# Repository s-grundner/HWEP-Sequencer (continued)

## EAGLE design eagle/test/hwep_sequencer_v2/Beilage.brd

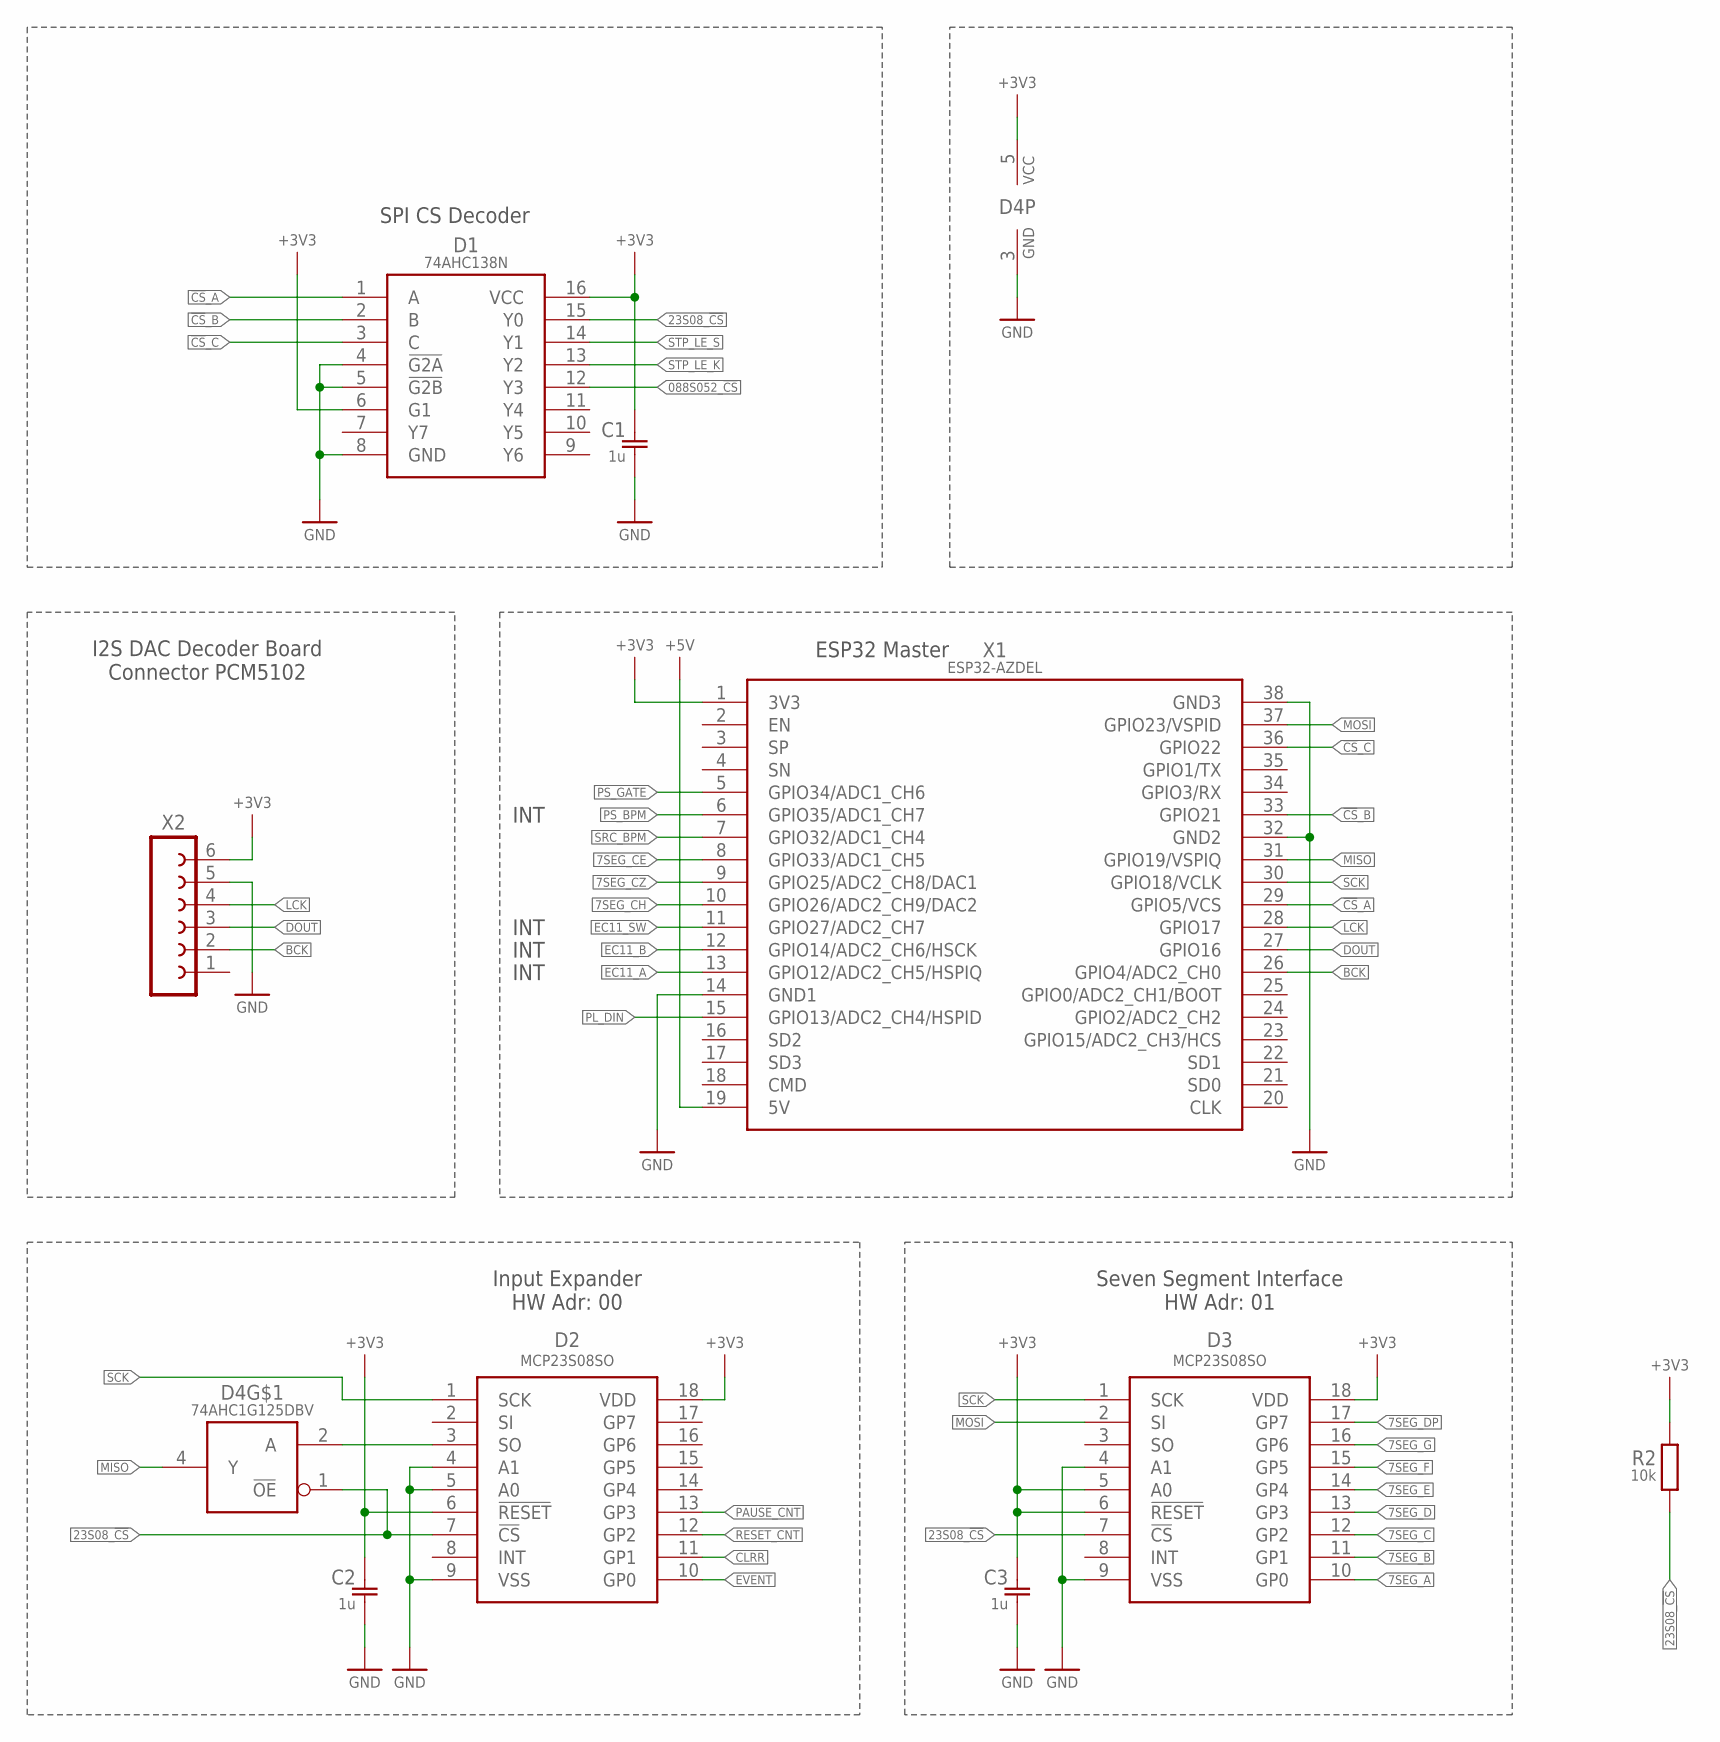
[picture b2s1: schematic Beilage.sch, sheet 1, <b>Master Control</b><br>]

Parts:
C1, C2, C3: 1u; C0805
D1: 74AHC138N; DIP16
D2, D3: MCP23S08SO; SO18W
D4: 74AHC1G125DBV; SOT23-5
R2: 10k; R0805
X1: ESP32-AZDEL
X2: FE06-1; FE06

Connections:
7SEG_A: D3.10 (GP0); also elsewhere on the board
7SEG_B: D3.11 (GP1); also elsewhere on the board
7SEG_C: D3.12 (GP2); also elsewhere on the board
7SEG_CE: X1.8 (GPIO33/ADC1_CH5); also elsewhere on the board
7SEG_CH: X1.10 (GPIO26/ADC2_CH9/DAC2); also elsewhere on the board
7SEG_CZ: X1.9 (GPIO25/ADC2_CH8/DAC1); also elsewhere on the board
7SEG_D: D3.13 (GP3); also elsewhere on the board
7SEG_DP: D3.17 (GP7); also elsewhere on the board
7SEG_E: D3.14 (GP4); also elsewhere on the board
7SEG_F: D3.15 (GP5); also elsewhere on the board
7SEG_G: D3.16 (GP6); also elsewhere on the board
23S08_!CS: D1.15 (Y0), D2.7 (!CS), D3.7 (!CS), D4.1 (!OE), R2.1
088S052_!CS!: D1.12 (Y3); also elsewhere on the board
!CS!_A: D1.1 (A), X1.29 (GPIO5/VCS)
!CS!_B: D1.2 (B), X1.33 (GPIO21)
!CS!_C: D1.3 (C), X1.36 (GPIO22)
+3V3: C1.1, C2.1, C3.1, D1.6 (G1), D1.16 (VCC), D2.6 (!RESET), D2.18 (VDD), D3.5 (A0), D3.6 (!RESET), D3.18 (VDD), D4.5 (VCC), R2.2, X1.1 (3V3), X2.6; also elsewhere on the board
+5V: X1.19 (5V); also elsewhere on the board
BCK: X1.26 (GPIO4/ADC2_CH0), X2.2
CLRR: D2.11 (GP1); also elsewhere on the board
DOUT: X1.27 (GPIO16), X2.3
EC11_A: X1.13 (GPIO12/ADC2_CH5/HSPIQ); also elsewhere on the board
EC11_B: X1.12 (GPIO14/ADC2_CH6/HSCK); also elsewhere on the board
EC11_SW: X1.11 (GPIO27/ADC2_CH7); also elsewhere on the board
EVENT: D2.10 (GP0); also elsewhere on the board
GND: C1.2, C2.2, C3.2, D1.4 (!G2A), D1.5 (!G2B), D1.8 (GND), D2.4 (A1), D2.5 (A0), D2.9 (VSS), D3.4 (A1), D3.9 (VSS), D4.3 (GND), X1.14 (GND1), X1.32 (GND2), X1.38 (GND3), X2.5; also elsewhere on the board
LCK: X1.28 (GPIO17), X2.4
MISO: D4.4 (Y), X1.31 (GPIO19/VSPIQ); also elsewhere on the board
MOSI: D3.2 (SI), X1.37 (GPIO23/VSPID); also elsewhere on the board
unnamed: D2.3 (SO), D4.2 (A)
PAUSE_CNT: D2.13 (GP3); also elsewhere on the board
PL_DIN: X1.15 (GPIO13/ADC2_CH4/HSPID); also elsewhere on the board
PS_BPM: X1.6 (GPIO35/ADC1_CH7); also elsewhere on the board
PS_GATE: X1.5 (GPIO34/ADC1_CH6); also elsewhere on the board
RESET_CNT: D2.12 (GP2); also elsewhere on the board
SCK: D2.1 (SCK), D3.1 (SCK), X1.30 (GPIO18/VCLK); also elsewhere on the board
SRC_BPM: X1.7 (GPIO32/ADC1_CH4); also elsewhere on the board
STP_LE_K: D1.13 (Y2); also elsewhere on the board
STP_LE_S: D1.14 (Y1); also elsewhere on the board

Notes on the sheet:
Seven Segment Interface HW Adr: 01
ESP32 Master
I2S DAC Decoder Board Connector PCM5102
INT
Input Expander HW Adr: 00
SPI CS Decoder

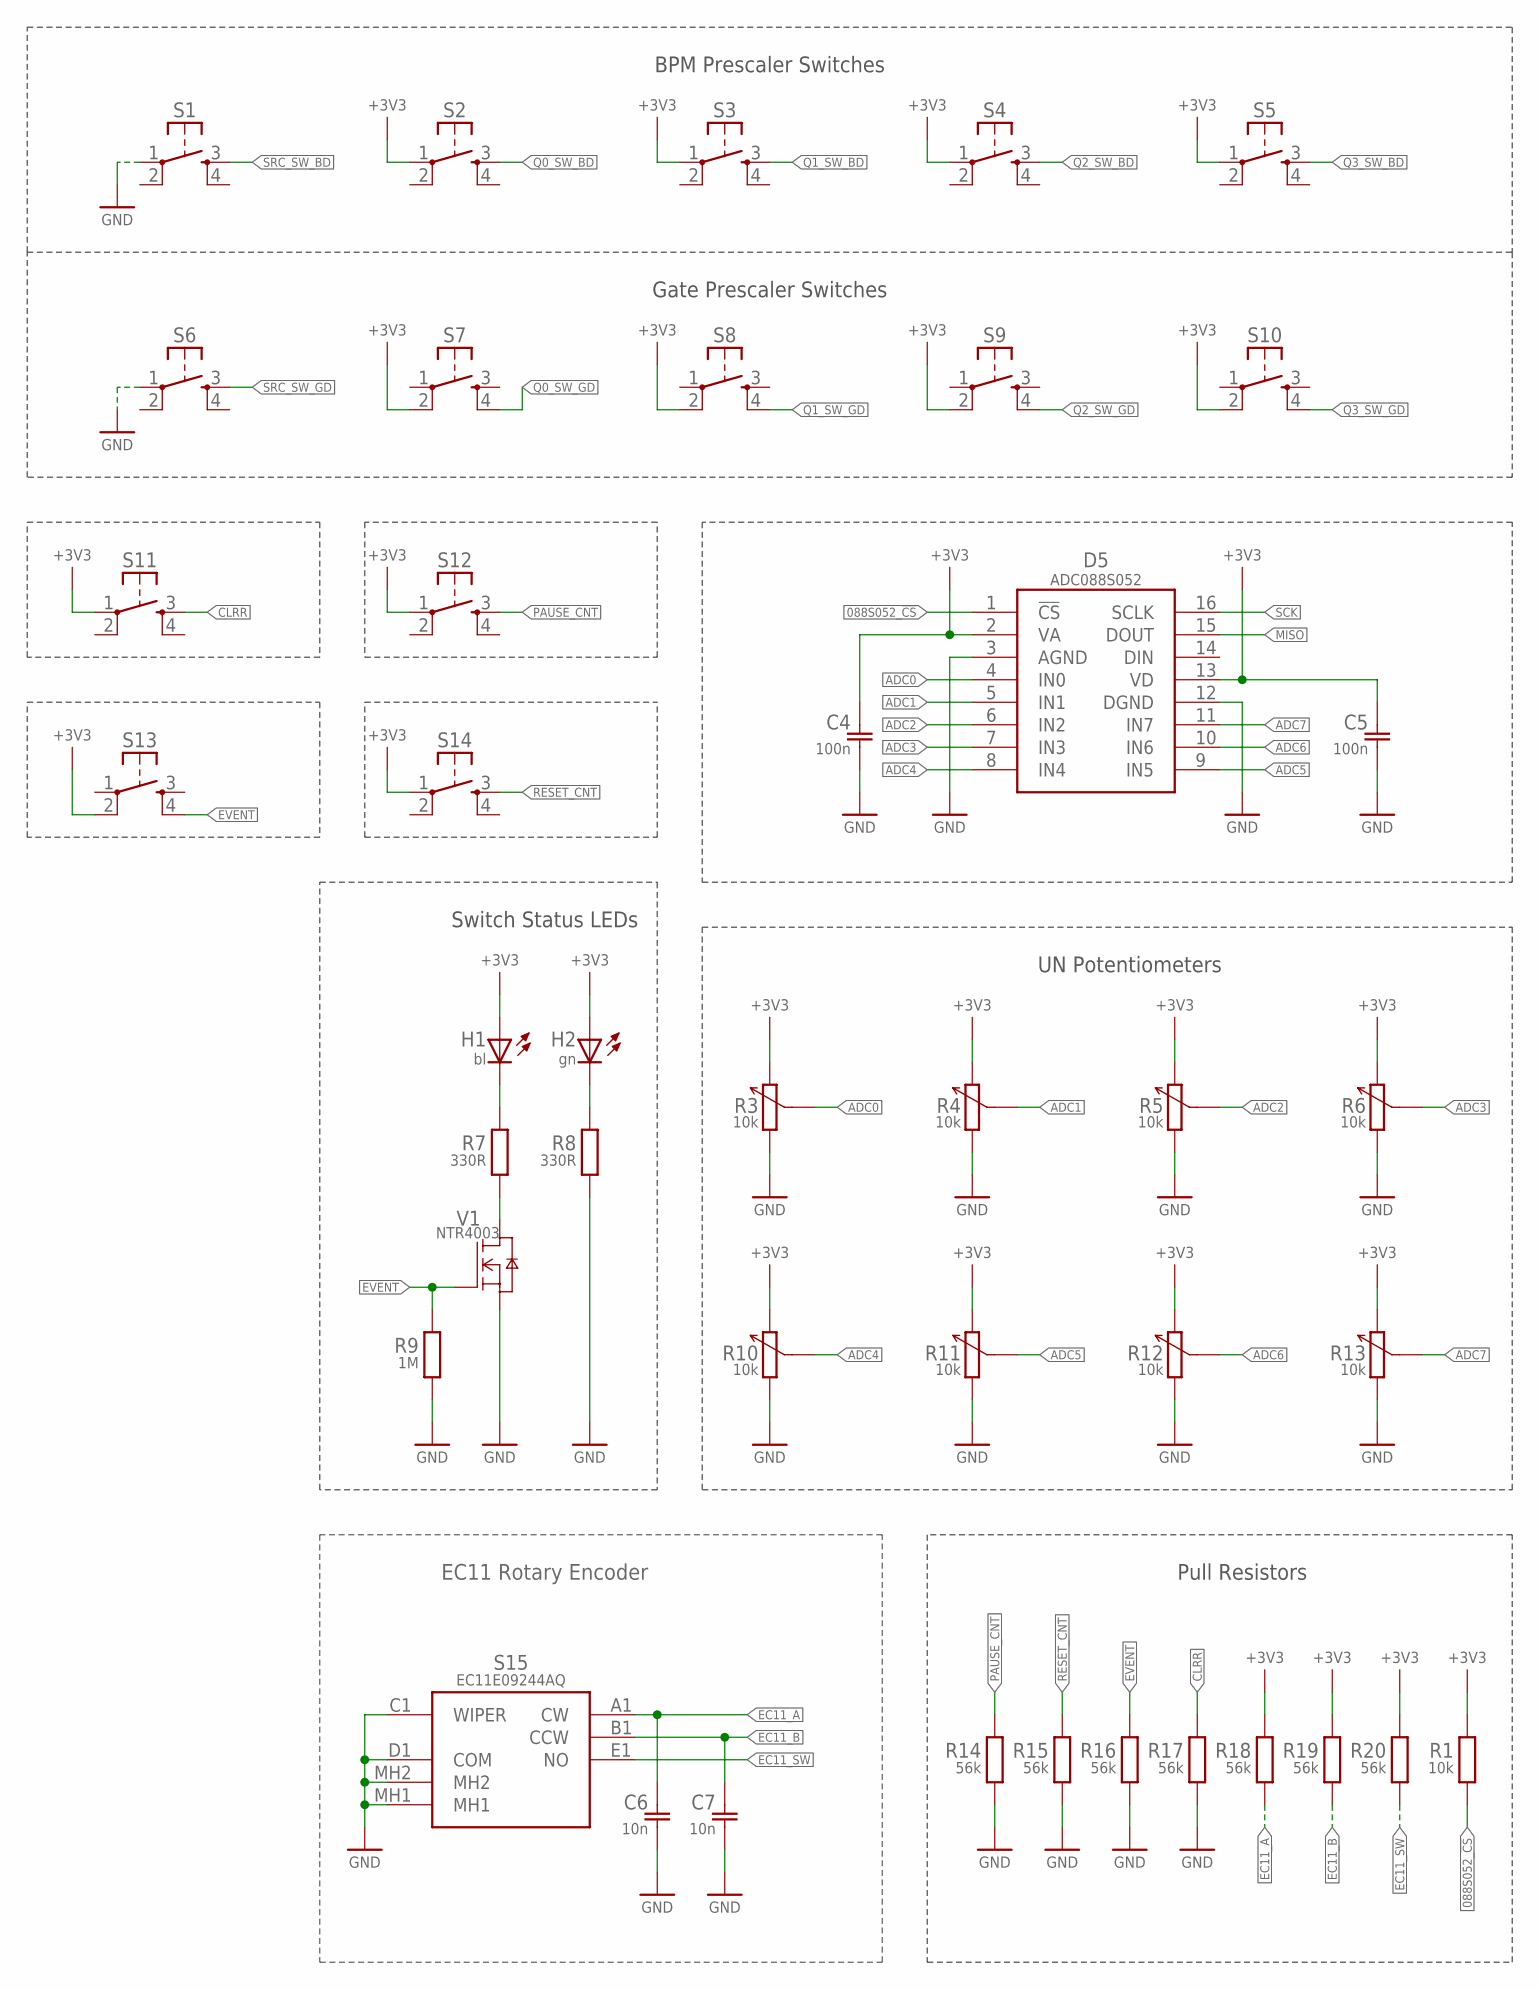
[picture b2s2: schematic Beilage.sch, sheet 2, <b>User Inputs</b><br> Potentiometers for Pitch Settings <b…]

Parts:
C4, C5: 100n; C0805
C6, C7: 10n; C0805
D5: ADC088S052; TSSOP16
H1: bl; CHIPLED_1206
H2: gn; CHIPLED_1206
R1: 10k; R0805
R3, R4, R5, R6, R10, R11, R12, R13: 10k; P160L
R7, R8: 330R; R0805
R9: 1M; R0805
R14, R15, R16, R17, R18, R19, R20: 56k; R0805
S1, S2, S3, S4, S5, S6, S7, S8, S9, S10, S11, S12, S13, S14: TASTE10XX; B3F-10XX
S15: EC11E09244AQ; EC11
V1: NTR4003; SOT23

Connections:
088S052_!CS!: D5.1 (!CS), R1.1; also elsewhere on the board
+3V3: C4.1, C5.1, D5.2 (VA), D5.13 (VD), H1.A, H2.A, R1.2, R3.3 (2), R4.3 (2), R5.3 (2), R6.3 (2), R10.3 (2), R11.3 (2), R12.3 (2), R13.3 (2), R18.2, R19.2, R20.2, S2.1, S3.1, S4.1, S5.1, S7.2 (P1), S8.2 (P1), S9.2 (P1), S10.2 (P1), S11.1, S12.1, S13.2 (P1), S14.1; also elsewhere on the board
ADC0: D5.4 (IN0), R3.2 (3)
ADC1: D5.5 (IN1), R4.2 (3)
ADC2: D5.6 (IN2), R5.2 (3)
ADC3: D5.7 (IN3), R6.2 (3)
ADC4: D5.8 (IN4), R10.2 (3)
ADC5: D5.9 (IN5), R11.2 (3)
ADC6: D5.10 (IN6), R12.2 (3)
ADC7: D5.11 (IN7), R13.2 (3)
CLRR: R17.2, S11.3 (S); also elsewhere on the board
EC11_A: C6.1, R18.1, S15.A1 (CW); also elsewhere on the board
EC11_B: C7.1, R19.1, S15.B1 (CCW); also elsewhere on the board
EC11_SW: R20.1, S15.E1 (NO); also elsewhere on the board
EVENT: R9.2, R16.2, S13.4 (S1), V1.1 (G); also elsewhere on the board
GND: C4.2, C5.2, C6.2, C7.2, D5.3 (AGND), D5.12 (DGND), R3.1, R4.1, R5.1, R6.1, R8.1, R9.1, R10.1, R11.1, R12.1, R13.1, R14.1, R15.1, R16.1, R17.1, S1.1, S6.1, S15.C1 (WIPER), S15.D1 (COM), S15.MH1, S15.MH2, V1.2 (S); also elsewhere on the board
MISO: D5.15 (DOUT); also elsewhere on the board
unnamed: H2.C, R8.2
unnamed: H1.C, R7.2
unnamed: R7.1, V1.3 (D)
PAUSE_CNT: R14.2, S12.3 (S); also elsewhere on the board
Q0_SW_BD: S2.3 (S); also elsewhere on the board
Q0_SW_GD: S7.4 (S1); also elsewhere on the board
Q1_SW_BD: S3.3 (S); also elsewhere on the board
Q1_SW_GD: S8.4 (S1); also elsewhere on the board
Q2_SW_BD: S4.3 (S); also elsewhere on the board
Q2_SW_GD: S9.4 (S1); also elsewhere on the board
Q3_SW_BD: S5.3 (S); also elsewhere on the board
Q3_SW_GD: S10.4 (S1); also elsewhere on the board
RESET_CNT: R15.2, S14.3 (S); also elsewhere on the board
SCK: D5.16 (SCLK); also elsewhere on the board
SRC_SW_BD: S1.3 (S); also elsewhere on the board
SRC_SW_GD: S6.3 (S); also elsewhere on the board

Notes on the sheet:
UN Potentiometers
Pull Resistors
EC11 Rotary Encoder
BPM Prescaler Switches
Gate Prescaler Switches
Switch Status LEDs

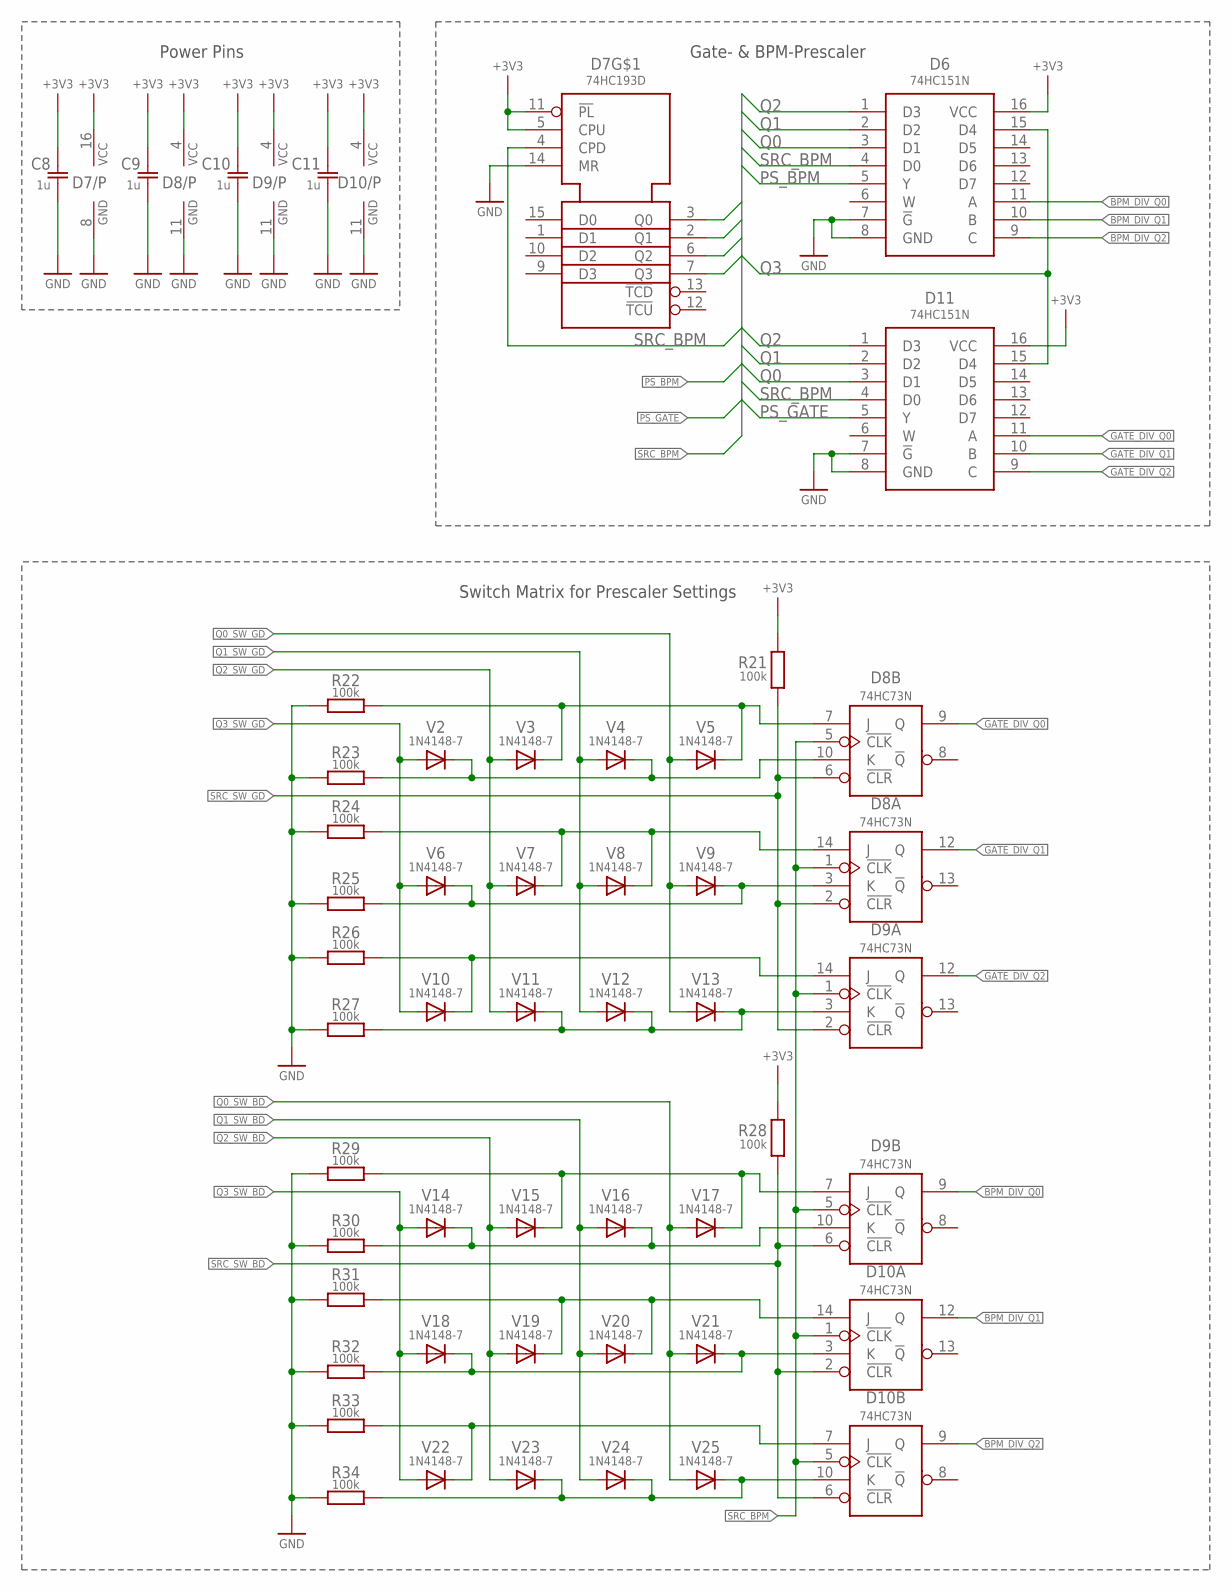
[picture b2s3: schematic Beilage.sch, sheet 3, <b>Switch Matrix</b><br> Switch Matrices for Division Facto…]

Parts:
C8, C9, C10, C11: 1u; C0805
D6, D11: 74HC151N; DIP16
D7: 74HC193D; SO16
D8, D9, D10: 74HC73N; DIP14
R21, R22, R23, R24, R25, R26, R27, R28, R29, R30, R31, R32, R33, R34: 100k; R0805
V2, V3, V4, V5, V6, V7, V8, V9, V10, V11, V12, V13, V14, V15, V16, V17, V18, V19, V20, V21, V22, V23, V24, V25: 1N4148-7; DO35-7

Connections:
+3V3: C8.1, C9.1, C10.1, C11.1, D6.16 (VCC), D7.5 (CPU), D7.11 (!PL), D7.16 (VCC), D8.4 (VCC), D9.4 (VCC), D10.4 (VCC), D11.16 (VCC), R21.2, R28.2; also elsewhere on the board
BPM_DIV_Q0: D6.11 (A), D9.9 (Q)
BPM_DIV_Q1: D6.10 (B), D10.12 (Q)
BPM_DIV_Q2: D6.9 (C), D10.9 (Q)
GATE_DIV_Q0: D8.9 (Q), D11.11 (A)
GATE_DIV_Q1: D8.12 (Q), D11.10 (B)
GATE_DIV_Q2: D9.12 (Q), D11.9 (C)
GND: C8.2, C9.2, C10.2, C11.2, D6.7 (!G), D6.8 (GND), D7.8 (GND), D7.14 (MR), D8.11 (GND), D9.11 (GND), D10.11 (GND), D11.7 (!G), D11.8 (GND), R22.1, R23.1, R24.1, R25.1, R26.1, R27.1, R29.1, R30.1, R31.1, R32.1, R33.1, R34.1; also elsewhere on the board
unnamed: D9.14 (J), R26.2, V10.C
unnamed: D8.10 (K), R23.2, V2.C, V4.C
unnamed: D8.14 (J), R24.2, V7.C, V8.C
unnamed: D8.7 (J), R22.2, V3.C, V5.C
unnamed: D9.3 (K), R27.2, V11.C, V12.C, V13.C
unnamed: D8.3 (K), R25.2, V6.C, V9.C
unnamed: D9.10 (K), R30.2, V14.C, V16.C
unnamed: D10.10 (K), R34.2, V23.C, V24.C, V25.C
unnamed: D10.7 (J), R33.2, V22.C
unnamed: D10.14 (J), R31.2, V19.C, V20.C
unnamed: D9.7 (J), R29.2, V15.C, V17.C
unnamed: D10.3 (K), R32.2, V18.C, V21.C
PS_BPM: D6.5 (Y); also elsewhere on the board
PS_GATE: D11.5 (Y); also elsewhere on the board
Q0: D6.3 (D1), D7.3 (Q0), D11.3 (D1)
Q0_SW_BD: V17.A, V21.A, V25.A; also elsewhere on the board
Q0_SW_GD: V5.A, V9.A, V13.A; also elsewhere on the board
Q1: D6.2 (D2), D7.2 (Q1), D11.2 (D2)
Q1_SW_BD: V16.A, V20.A, V24.A; also elsewhere on the board
Q1_SW_GD: V4.A, V8.A, V12.A; also elsewhere on the board
Q2: D6.1 (D3), D7.6 (Q2), D11.1 (D3)
Q2_SW_BD: V15.A, V19.A, V23.A; also elsewhere on the board
Q2_SW_GD: V3.A, V7.A, V11.A; also elsewhere on the board
Q3: D6.15 (D4), D7.7 (Q3), D11.15 (D4)
Q3_SW_BD: V14.A, V18.A, V22.A; also elsewhere on the board
Q3_SW_GD: V2.A, V6.A, V10.A; also elsewhere on the board
SRC_BPM: D6.4 (D0), D7.4 (CPD), D8.1 (!CLK), D8.5 (!CLK), D9.1 (!CLK), D9.5 (!CLK), D10.1 (!CLK), D10.5 (!CLK), D11.4 (D0); also elsewhere on the board
SRC_SW_BD: D9.6 (!CLR), D10.2 (!CLR), D10.6 (!CLR), R28.1; also elsewhere on the board
SRC_SW_GD: D8.2 (!CLR), D8.6 (!CLR), D9.2 (!CLR), R21.1; also elsewhere on the board

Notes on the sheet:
Gate- & BPM-Prescaler
Switch Matrix for Prescaler Settings
Power Pins

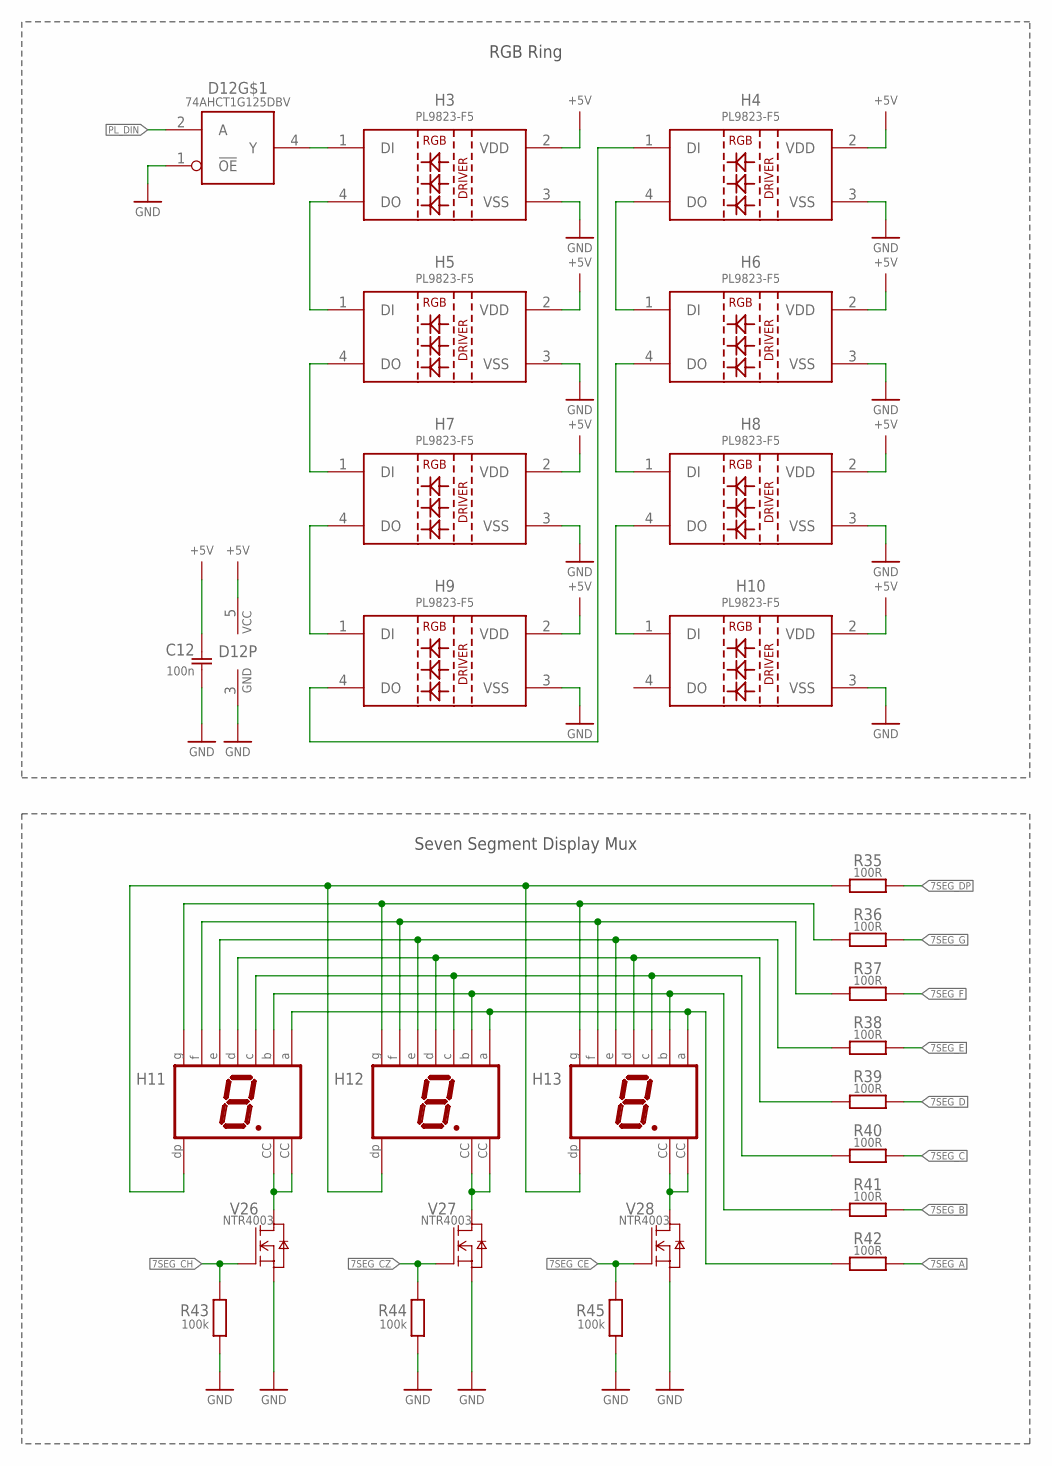
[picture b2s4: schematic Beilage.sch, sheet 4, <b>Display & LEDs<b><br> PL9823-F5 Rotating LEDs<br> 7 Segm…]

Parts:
C12: 100n; C0805
D12: 74AHCT1G125DBV; SOT23-5
H3, H4, H5, H6, H7, H8, H9, H10: PL9823-F5; LED-PL9823-F5
H11, H12, H13: HD-H103; HDSP-E
R35, R36, R37, R38, R39, R40, R41, R42: 100R; R0805
R43, R44, R45: 100k; R0805
V26, V27, V28: NTR4003; SOT23

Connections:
7SEG_A: R42.2; also elsewhere on the board
7SEG_B: R41.2; also elsewhere on the board
7SEG_C: R40.2; also elsewhere on the board
7SEG_CE: R45.2, V28.1 (G); also elsewhere on the board
7SEG_CH: R43.2, V26.1 (G); also elsewhere on the board
7SEG_CZ: R44.2, V27.1 (G); also elsewhere on the board
7SEG_D: R39.2; also elsewhere on the board
7SEG_DP: R35.2; also elsewhere on the board
7SEG_E: R38.2; also elsewhere on the board
7SEG_F: R37.2; also elsewhere on the board
7SEG_G: R36.2; also elsewhere on the board
+5V: C12.1, D12.5 (VCC), H3.2 (VDD), H4.2 (VDD), H5.2 (VDD), H6.2 (VDD), H7.2 (VDD), H8.2 (VDD), H9.2 (VDD), H10.2 (VDD); also elsewhere on the board
GND: C12.2, D12.1 (!OE), D12.3 (GND), H3.3 (VSS), H4.3 (VSS), H5.3 (VSS), H6.3 (VSS), H7.3 (VSS), H8.3 (VSS), H9.3 (VSS), H10.3 (VSS), R43.1, R44.1, R45.1, V26.2 (S), V27.2 (S), V28.2 (S); also elsewhere on the board
unnamed: H4.1 (DI), H9.4 (DO)
unnamed: H11.DP, H12.DP, H13.DP, R35.1
unnamed: D12.4 (Y), H3.1 (DI)
unnamed: H11.G, H12.G, H13.G, R36.1
unnamed: H11.F, H12.F, H13.F, R37.1
unnamed: H11.A, H12.A, H13.A, R42.1
unnamed: H11.B, H12.B, H13.B, R41.1
unnamed: H11.CC1 (CC), H11.CC2 (CC), V26.3 (D)
unnamed: H11.D, H12.D, H13.D, R39.1
unnamed: H4.4 (DO), H6.1 (DI)
unnamed: H6.4 (DO), H8.1 (DI)
unnamed: H8.4 (DO), H10.1 (DI)
unnamed: H12.CC1 (CC), H12.CC2 (CC), V27.3 (D)
unnamed: H13.CC1 (CC), H13.CC2 (CC), V28.3 (D)
unnamed: H3.4 (DO), H5.1 (DI)
unnamed: H5.4 (DO), H7.1 (DI)
unnamed: H7.4 (DO), H9.1 (DI)
unnamed: H11.C, H12.C, H13.C, R40.1
unnamed: H11.E, H12.E, H13.E, R38.1
PL_DIN: D12.2 (A); also elsewhere on the board

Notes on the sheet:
Seven Segment Display Mux
RGB Ring

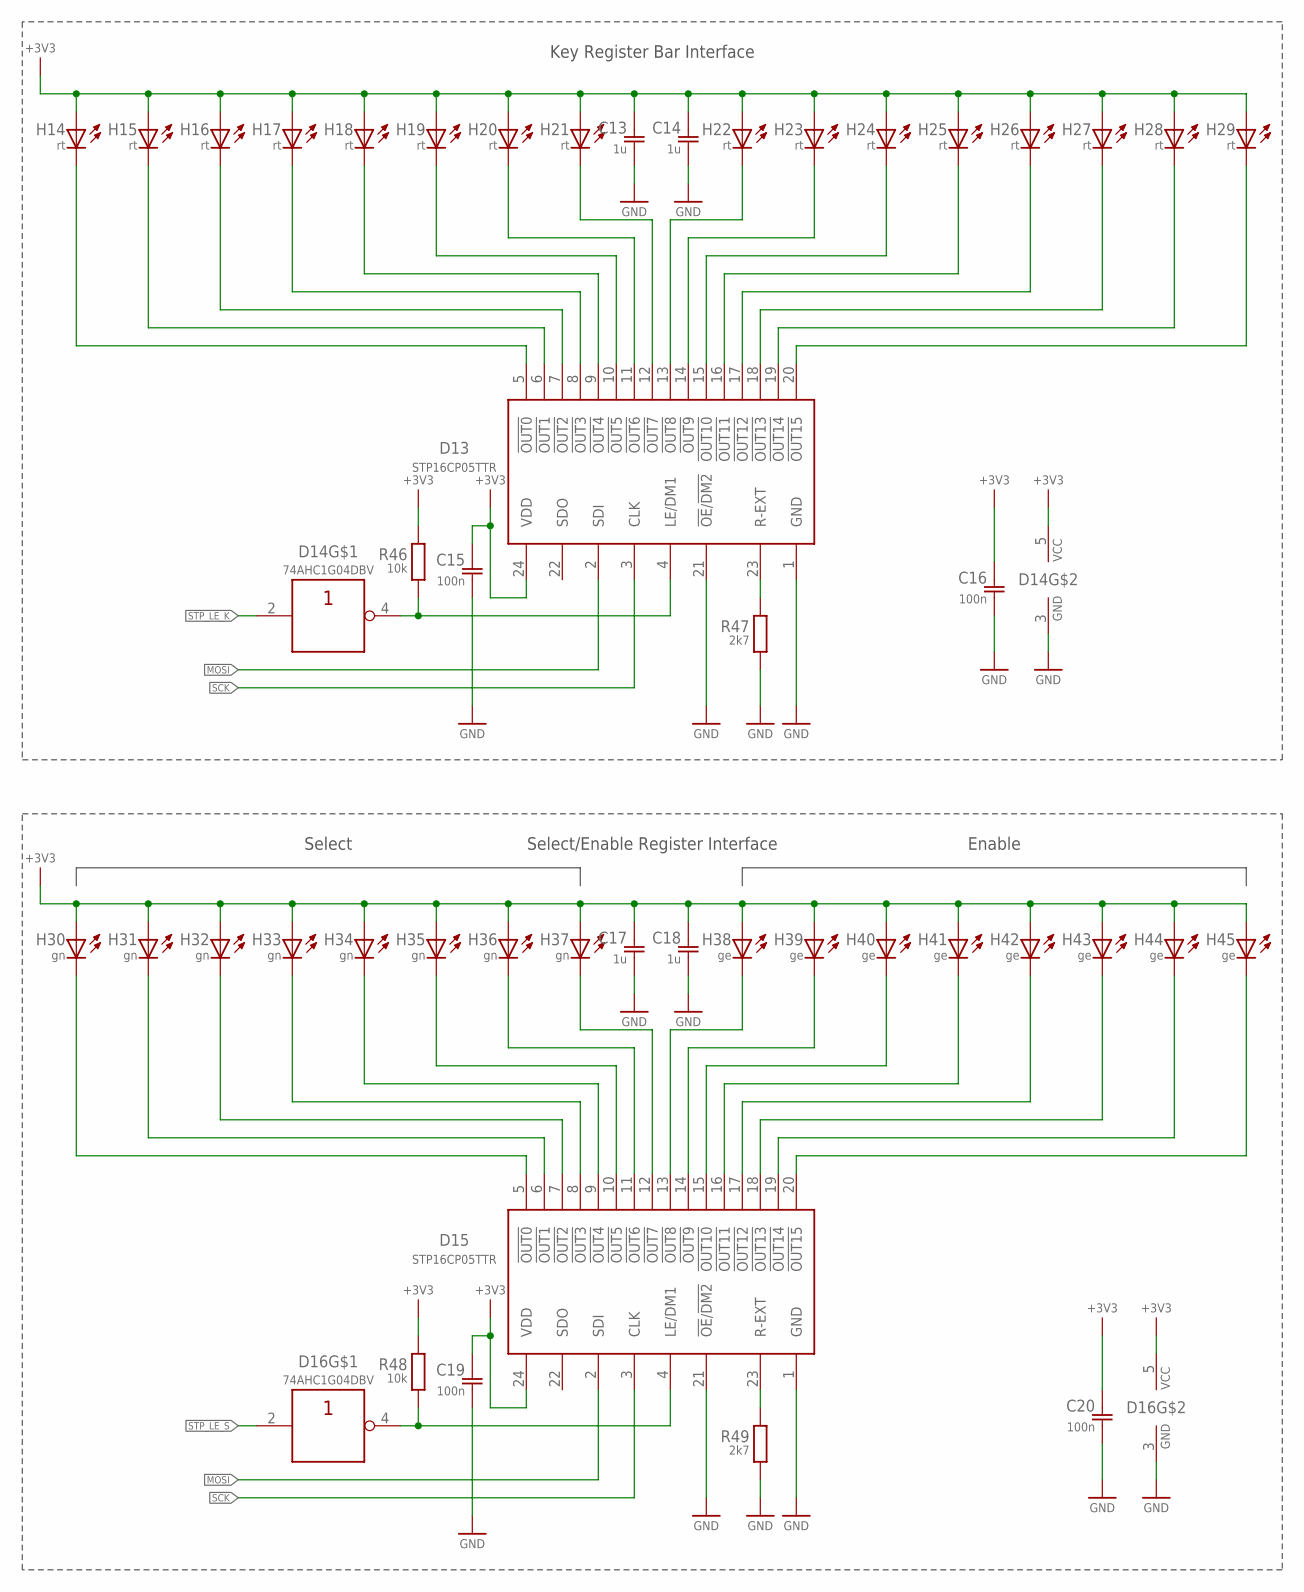
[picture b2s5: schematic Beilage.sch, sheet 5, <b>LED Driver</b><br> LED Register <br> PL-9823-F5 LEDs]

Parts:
C13, C14, C17, C18: 1u; C0805
C15, C16, C19, C20: 100n; C0805
D13, D15: STP16CP05TTR; TSSOP24
D14, D16: 74AHC1G04DBV; SOT23-5
H14, H15, H16, H17, H18, H19, H20, H21, H22, H23, H24, H25, H26, H27, H28, H29: rt; CHIPLED_1206
H30, H31, H32, H33, H34, H35, H36, H37: gn; LED5MM
H38, H39, H40, H41, H42, H43, H44, H45: ge; LED5MM
R46, R48: 10k; R0805
R47, R49: 2k7; R0805

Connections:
+3V3: C13.1, C14.1, C15.1, C16.1, C17.1, C18.1, C19.1, C20.1, D13.24 (VDD), D14.5 (VCC), D15.24 (VDD), D16.5 (VCC), H14.A, H15.A, H16.A, H17.A, H18.A, H19.A, H20.A, H21.A, H22.A, H23.A, H24.A, H25.A, H26.A, H27.A, H28.A, H29.A, H30.A, H31.A, H32.A, H33.A, H34.A, H35.A, H36.A, H37.A, H38.A, H39.A, H40.A, H41.A, H42.A, H43.A, H44.A, H45.A, R46.2, R48.2; also elsewhere on the board
GND: C13.2, C14.2, C15.2, C16.2, C17.2, C18.2, C19.2, C20.2, D13.1 (GND), D13.21 (!OE!/!DM2), D14.3 (GND), D15.1 (GND), D15.21 (!OE!/!DM2), D16.3 (GND), R47.1, R49.1; also elsewhere on the board
MOSI: D13.2 (SDI), D15.2 (SDI); also elsewhere on the board
unnamed: D13.5 (!OUT0), H14.C
unnamed: D13.6 (!OUT1), H15.C
unnamed: D13.7 (!OUT2), H16.C
unnamed: D13.8 (!OUT3), H17.C
unnamed: D13.9 (!OUT4), H18.C
unnamed: D13.10 (!OUT5), H19.C
unnamed: D13.11 (!OUT6), H20.C
unnamed: D13.12 (!OUT7), H21.C
unnamed: D13.23 (R-EXT), R47.2
unnamed: D13.13 (!OUT8), H22.C
unnamed: D13.14 (!OUT9), H23.C
unnamed: D13.15 (!OUT10), H24.C
unnamed: D13.16 (!OUT11), H25.C
unnamed: D13.17 (!OUT12), H26.C
unnamed: D13.18 (!OUT13), H27.C
unnamed: D13.19 (!OUT14), H28.C
unnamed: D13.20 (!OUT15), H29.C
unnamed: D15.5 (!OUT0), H30.K (C)
unnamed: D15.6 (!OUT1), H31.K (C)
unnamed: D15.7 (!OUT2), H32.K (C)
unnamed: D15.8 (!OUT3), H33.K (C)
unnamed: D15.9 (!OUT4), H34.K (C)
unnamed: D15.10 (!OUT5), H35.K (C)
unnamed: D15.11 (!OUT6), H36.K (C)
unnamed: D15.12 (!OUT7), H37.K (C)
unnamed: D15.13 (!OUT8), H38.K (C)
unnamed: D15.14 (!OUT9), H39.K (C)
unnamed: D15.15 (!OUT10), H40.K (C)
unnamed: D15.16 (!OUT11), H41.K (C)
unnamed: D15.17 (!OUT12), H42.K (C)
unnamed: D15.18 (!OUT13), H43.K (C)
unnamed: D15.19 (!OUT14), H44.K (C)
unnamed: D15.20 (!OUT15), H45.K (C)
unnamed: D15.23 (R-EXT), R49.2
unnamed: D15.4 (LE/DM1), D16.4 (Y), R48.1
unnamed: D13.4 (LE/DM1), D14.4 (Y), R46.1
SCK: D13.3 (CLK), D15.3 (CLK); also elsewhere on the board
STP_LE_K: D14.2 (A); also elsewhere on the board
STP_LE_S: D16.2 (A); also elsewhere on the board

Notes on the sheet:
Key Register Bar Interface
Select
Enable
Select/Enable Register Interface

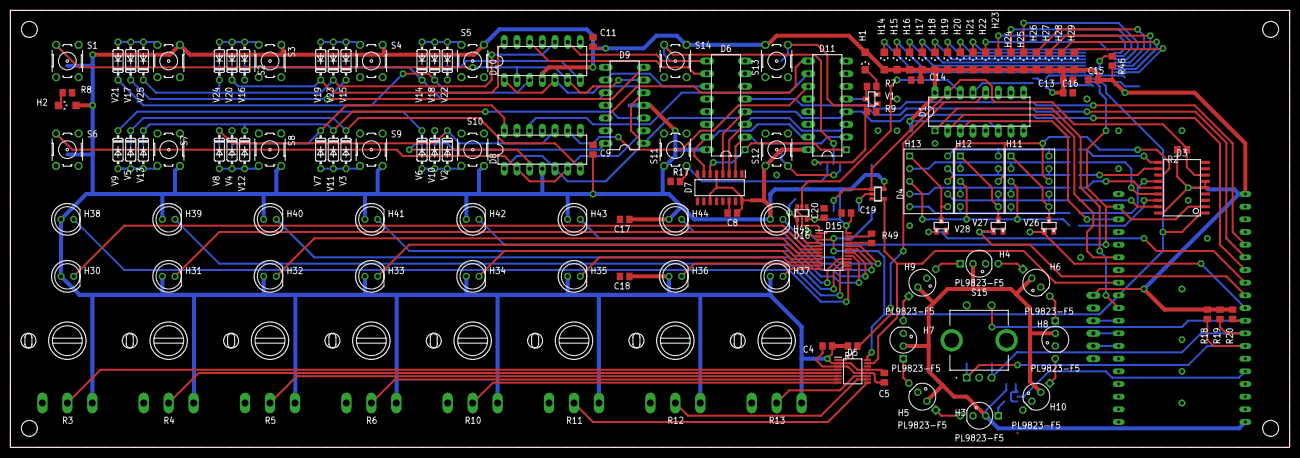
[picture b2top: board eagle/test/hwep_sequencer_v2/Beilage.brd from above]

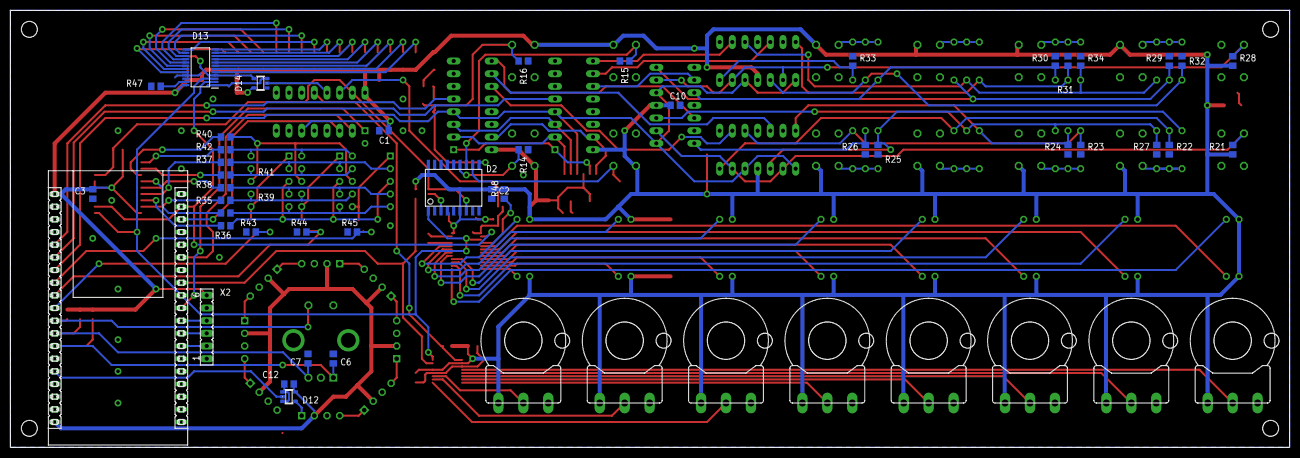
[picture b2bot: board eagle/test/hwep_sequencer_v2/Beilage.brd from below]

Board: 2 copper layers, 256.5 x 87.6 mm, 175 parts (43 on the bottom side), 137 nets.

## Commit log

2022-01-13 init dev branch
2022-01-13 cleanup
2022-01-14 Board: Bedruck Formatiert
    Board Optimiert und Layer:
    Names
    Values
    Formatiert
2022-01-14 cleanup old versions
2022-01-14 Prototype Board
2022-01-15 Board Prototyp Fertiggestellt
    Fehlende Entkoppel-Kondensatoren eingefügt
    Bestückungsdruck überarbeitet und Formatiert
2022-01-16 RGB Ring now in SMD
    SMD RGB LEDS WS2812 used because of availability
    PSU Buck Converter 12v to 5v still to be added to the schematic
2022-01-17 Optimized Wires
2022-01-20 Major Prescaler Update
    Optimized Prescaler:
    Now Fully Software side.
    Inputs are priority encoded and put on MCP23S08 free input pins.
    Issues:
    Analog Reference Voltage Needed?
    Dedicated PSU / Voltage converter
2022-01-20 fixed traces
2022-01-21 Documentation Update
    Added STL
    cleaned up docs
2022-01-24 Bilder
    Schaltplan
2022-01-24 Schematic Pictures
    and word file for Printing
2022-01-24 sim and docu
    Updated BOM
    Prescaler Logisim Simulation
2022-01-25 Prescaler Sim
    Optimised Schematic
    Changed unavailable ICs
    Issue: Interrupt on Input MCP23S08 and Prescaler Strobe
2022-01-25 upd BOM
2022-01-25 Updated BOM
2022-01-26 IDF test
2022-01-27 upd gitignore
2022-01-31 Test_I2C
2022-01-31 deleted mül
2022-02-06 i2s testing & KUB
2022-02-07 final commit before testing
2022-02-07 removed key register visualisation
    bloat feature
2022-02-07 upd doku
2022-02-07 upt Docu
2022-02-09 removed unnecessary features
2022-02-13 spi test
2022-02-14 mcp23s08 implemented
2022-02-15 reroute brd complete
2022-02-15 optimized brd and 3d model
2022-02-17 lang
2022-02-17 updated outline
2022-02-18 mcp interrupt upd
2022-02-22 Finalised Board
2022-02-25 ec11 rotary encoder tested
    relative rot angle/position and switch callback
2022-02-25 ec11 testing
2022-02-25 finale gerber generation
2022-02-25 removed trash references and deprecated files
2022-02-28 Update adc
2022-03-01 encoder + adc upd
2022-03-02 updated ec11 package
2022-03-06 i2s variable frequency
    + board finalized and ordered
    + i2s variable frequency tested
2022-03-06 audio
    + i2s all waveforms functional
    + i2s variable frequency
    + encoder updated (now with pushbutton counter)
2022-03-06 upd i2s
2022-03-09 waveform cutoff fix
2022-03-10 include upd
2022-03-10 cleaner way to write frequencies
    added oscillators
2022-03-21 first device test (large commit)
2022-03-24 demo program upd
2022-03-24 upd ws2812b lib
2022-03-28 upd to 28.03.2022
2022-03-31 fixed spi bus driver
2022-04-04 led strip upd
2022-04-04 hwep 20220404
2022-04-25 timer dycle started
2022-05-03 added synth functions and upd demo main version
    sequencer header
2022-05-05 upd synth
2022-05-06 upd main
2022-05-06 upd includes
2022-05-09 hwep lession upd
2022-05-30 fix bugs
2022-06-03 upd sqc header
2022-06-09 fixed seven segment muxing
    issue #41 fixed
2022-06-09 upd BSB & cleanup
2022-06-12 Added Button Control
    Implemented MCP interrupt for Buttons.
    Prescaler for Gate and BPM as well as 4 main buttons are now saved in the sequencer_handle_t on change
2022-06-13 upd buttons
    Still need to fix issue #45
2022-06-13 Doku
2022-06-13 hwep 20221306
    added semaphores
    #45 not fixed
2022-06-13 upd semaphores
2022-06-13 fixed a few
    # fixed #40
    # partly fixed #45:
    this occurs because of the fast display multiplexing -> timer interrupts spi transmissin or the other way around. ESP either crashes or th ebutton inputs are read in a weird way (no MSB read but stil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
2022-06-14 upd ENR mode
    ENR mode now resets on cursor but only if mode is other than ENR.
    ADC to pitch fix
2022-06-14 upd button functions
2022-06-15 RTOS IS NOT NICE TO ME
    RTOS NEEDS MAJOR FIX
    spi bus transaction timings need to be scheduled correctls
    UPDATE
    updated ENR button funct a little bit
2022-06-17 a guada dic test
2022-06-17 implemented RTOS functions
    new mode Timer
    fixed #48 #47
    Started Software Documentatino
2022-06-18 upd diagrams
2022-06-18 updated functionality
    issue #50 still present
2022-06-18 fixed
    less ISR calls fixed #50
2022-06-18 cleanup and doku
2022-06-18 Doku Software
2022-06-18 exprt pro
2022-06-18 Docu PCB
2022-06-18 added dark sw assets
2022-06-18 cleanup and SW docs upd
2022-06-19 docu print
2022-06-19 finished FUB
    except KEY mode, everything is completed for now
2022-06-19 clean up and finished word docs
2022-06-20 upd docs
2022-06-20 added pdf embedder
2022-08-11 upd hwdocs
2022-10-11 added knob
2023-06-12 upd libs
2023-11-04 added prototype functions in main
    cleanup repetetive code
2026-01-23 Add Apache License 2.0
    Added the Apache License 2.0 to the project.
